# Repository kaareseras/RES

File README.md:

It's like a swiss army knife :-)

Features

- ESP32 on an NodeMCU board, supporting WiFi, Bluetooth
- AI Thinker A7 supporting WiFi, GPS and GPRS
- Releay for controlling almost anything
- SD-card for storing data while offline
- Voltage regulator supporting input from 5-30 Volt

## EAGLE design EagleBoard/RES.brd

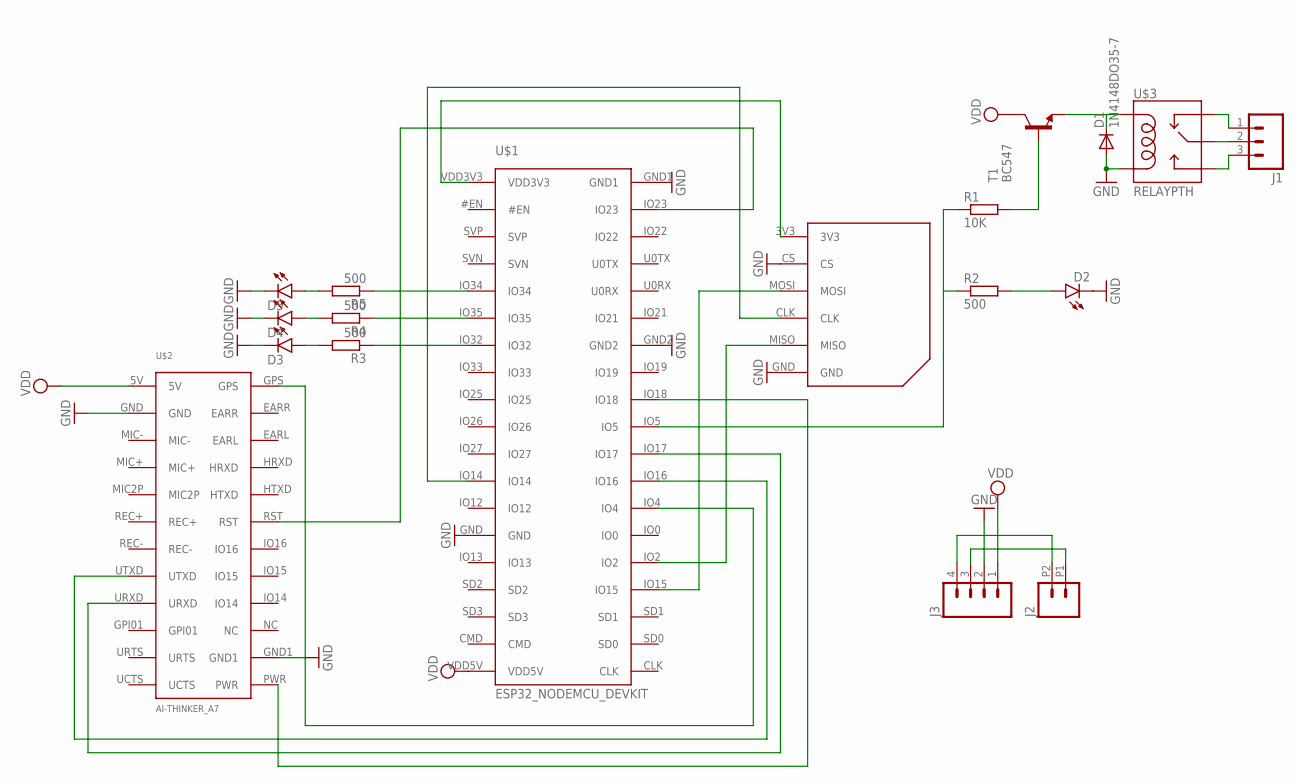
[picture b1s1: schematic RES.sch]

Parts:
D1: 1N4148DO35-7; DO35-7
D2, D3, D4, D5: LED3MM
J1: M03-SCREW-5MM; SCREWTERMINAL-5MM-3
J2: M022.54MM_SCREWTERM; 1X02_2.54_SCREWTERM
J3: M04SCREW; SCREWTERMINAL-3.5MM-4
R1: 10K; 0204/7
R2, R3, R4, R5: 500; 0204/7
T1: BC547; TO92
U$1: ESP32_NODEMCU_DEVKIT; ESP32_NODEMCU_PACKAGE
U$2: AI-THINKER_A7; AI-THINKER_A7_PAC
U$3: RELAYPTH; SRD-05VDC-SL-C
U$4: SD-CARD_BREAKOUT; SD-CARD_BREAKOUT_PACK

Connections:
GND: D1.A, D2.K (C), D3.K (C), D4.K (C), D5.K (C), J3.2, U$1.GND, U$1.GND1, U$1.GND2, U$2.GND, U$2.GND1, U$3.COIL0, U$4.CS, U$4.GND
unnamed: J1.1, U$3.SWCLOSED (SWCLOSE)
unnamed: R1.1, R2.1, U$1.IO5
unnamed: U$1.IO18, U$2.PWR
unnamed: U$1.IO17, U$2.URXD
unnamed: U$1.IO16, U$2.UTXD
unnamed: U$1.IO4, U$2.GPS
unnamed: R1.2, T1.2 (B)
unnamed: D1.C, T1.1 (E), U$3.COIL1
unnamed: J1.2, U$3.SWCOMMON
unnamed: D2.A, R2.2
unnamed: J1.3, U$3.SWOPEN
unnamed: U$1.IO23, U$2.RST
unnamed: J2.P1 (1), J3.3
unnamed: J2.P2 (2), J3.4
unnamed: U$1.VDD3V3, U$4.3V3
unnamed: U$1.IO15, U$4.MOSI
unnamed: U$1.IO14, U$4.CLK
unnamed: U$1.IO2, U$4.MISO
unnamed: D3.A, R3.2
unnamed: D4.A, R4.2
unnamed: D5.A, R5.2
unnamed: R5.1, U$1.IO34
unnamed: R4.1, U$1.IO35
unnamed: R3.1, U$1.IO32
VDD: J3.1, T1.3 (C), U$1.VDD5V, U$2.5V

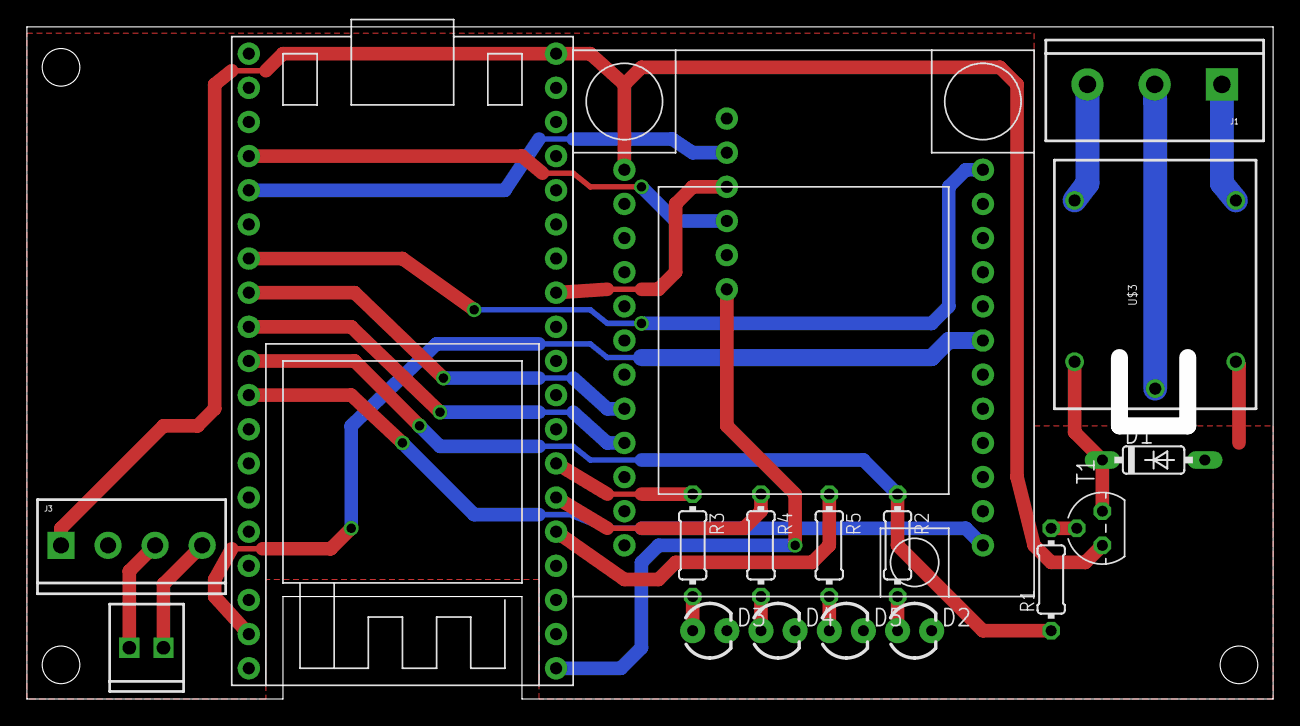
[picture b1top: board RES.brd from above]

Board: 2 copper layers, 91.4 x 48.7 mm, 18 parts (1 on the bottom side), 26 nets.

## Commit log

2017-10-22 Eagle files added
2017-10-22 Added arduino skecth
2017-10-22 Layout update
2017-10-24 Activate relay after boot according to last state
2017-10-29 Typo
2018-04-03 Test

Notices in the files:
parts and their libraries:
SparkFun-Connectors: Licensing: Creative Commons ShareAlike 4.0 International - https://creativecommons.org/licenses/by-sa/4.0
